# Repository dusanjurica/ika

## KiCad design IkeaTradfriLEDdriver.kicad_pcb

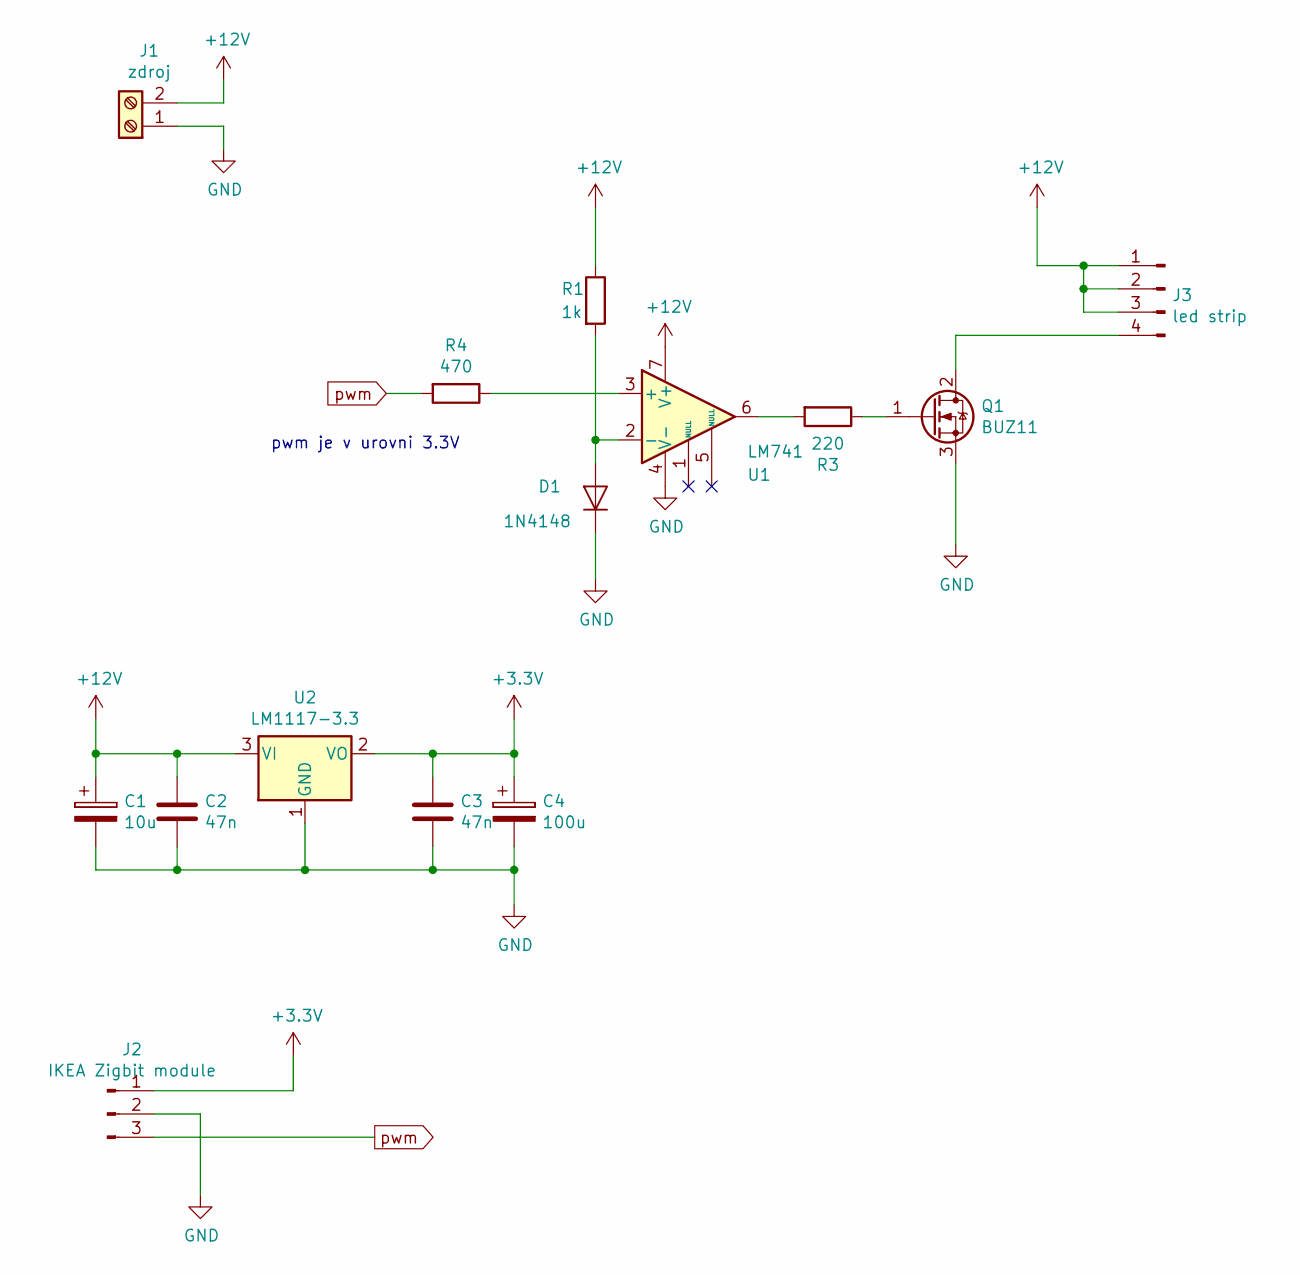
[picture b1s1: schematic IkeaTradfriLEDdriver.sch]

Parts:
C1: 10u; CP_Radial_D5.0mm_P2.50mm
C2, C3: 47n; C_Rect_L7.0mm_W2.0mm_P5.00mm
C4: 100u; CP_Radial_D8.0mm_P5.00mm
D1: 1N4148; D_DO-35_SOD27_P7.62mm_Horizontal
J1: zdroj; TerminalBlock_Altech_AK300-2_P5.00mm
J2: IKEA Zigbit module; PinHeader_1x03_P1.27mm_Vertical
J3: led strip; PinHeader_1x04_P2.54mm_Horizontal
Q1: BUZ11; TO-220-3_Vertical
R1: 1k; R_Axial_DIN0309_L9.0mm_D3.2mm_P12.70mm_Horizontal
R3: 220; R_Axial_DIN0309_L9.0mm_D3.2mm_P12.70mm_Horizontal
R4: 470; R_Axial_DIN0204_L3.6mm_D1.6mm_P7.62mm_Horizontal
U1: LM741; DIP-8_W10.16mm_LongPads
U2: LM1117-3.3; TO-220-3_Vertical

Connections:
+3V3: C3.1, C4.1, J2.1, U2.2 (VO)
+12V: C1.1, C2.1, J1.2, J3.1, J3.2, J3.3, R1.1, U1.7 (V+), U2.3 (VI)
GND: C1.2, C2.2, C3.2, C4.2, D1.1 (K), J1.1, J2.2, Q1.3 (S), U1.4 (V-), U2.1 (GND)
unnamed: D1.2 (A), R1.2, U1.2 (-)
unnamed: J3.4, Q1.2 (D)
unnamed: Q1.1 (G), R3.1
unnamed: R3.2, U1.6
unnamed: R4.1, U1.3 (+)
pwm: J2.3, R4.2

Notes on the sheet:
pwm je v urovni 3.3V

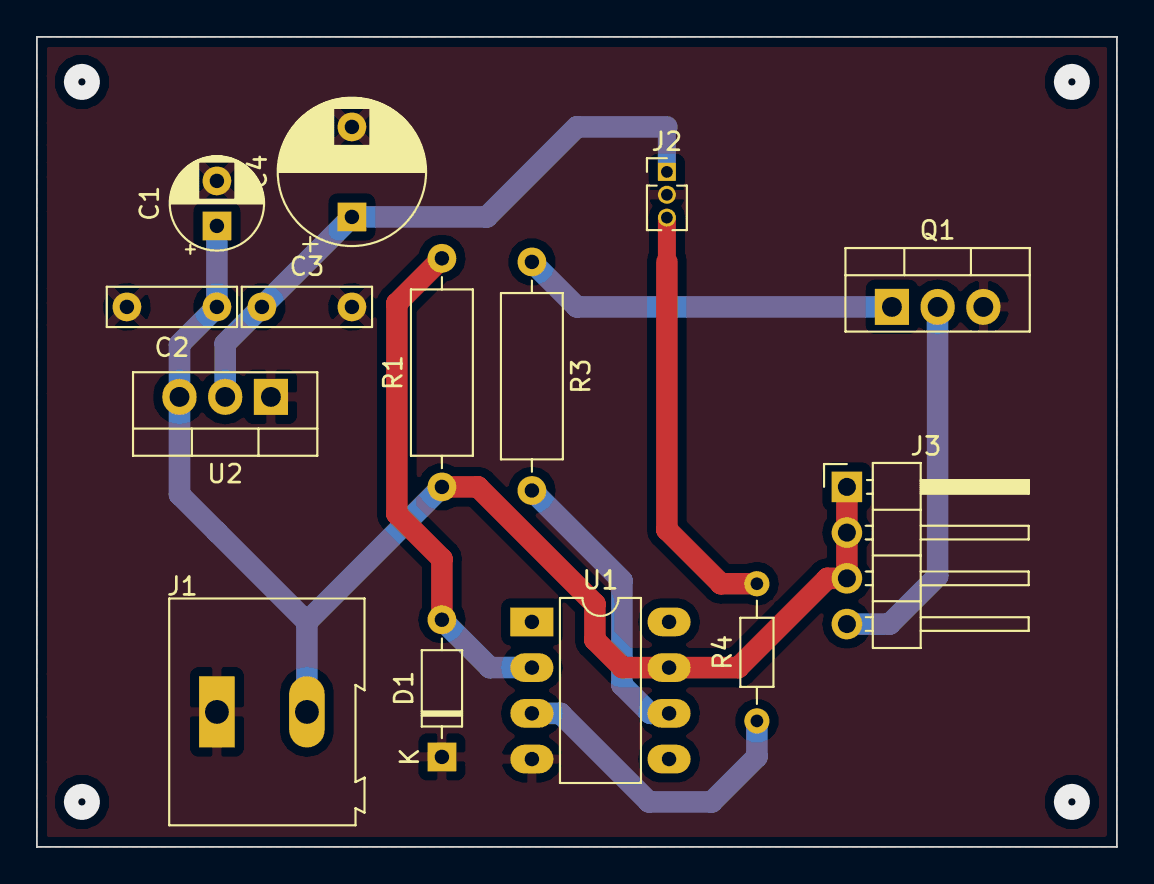
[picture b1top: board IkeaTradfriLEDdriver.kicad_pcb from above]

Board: 2 copper layers, 60.0 x 45.0 mm, 14 parts (0 on the bottom side), 9 nets.

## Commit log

2019-02-26 pokusy na desce
2019-02-26 Smazat nepotrebne soubory
2019-02-26 Pridany regulator lm1117 z 12V na 3.3V
2019-02-26 Pinheader pro Ikea zigbit module
2019-02-26 Dodelane schema Prirazena pouzdra Vytvoreny netlist Vygenerovana deska
2019-02-26 Naroutovana deska
2019-02-27 Deska naroutovana jako jednovrstva, vsechny cesty na spodku
2019-02-27 Provedene opravy na desce
2019-02-27 Chybejici rezistor, opravene schema
2019-02-28 Nejake divoke a nepovedene upravy
    Stahoval jsem aktualizaci 3d modelu, ale do slozky se neda zapsat, takze 6 hodin cekani a smula :(
2019-02-28 Pokusy s gerber soubory
2019-02-28 Nova deska + gerber soubory
